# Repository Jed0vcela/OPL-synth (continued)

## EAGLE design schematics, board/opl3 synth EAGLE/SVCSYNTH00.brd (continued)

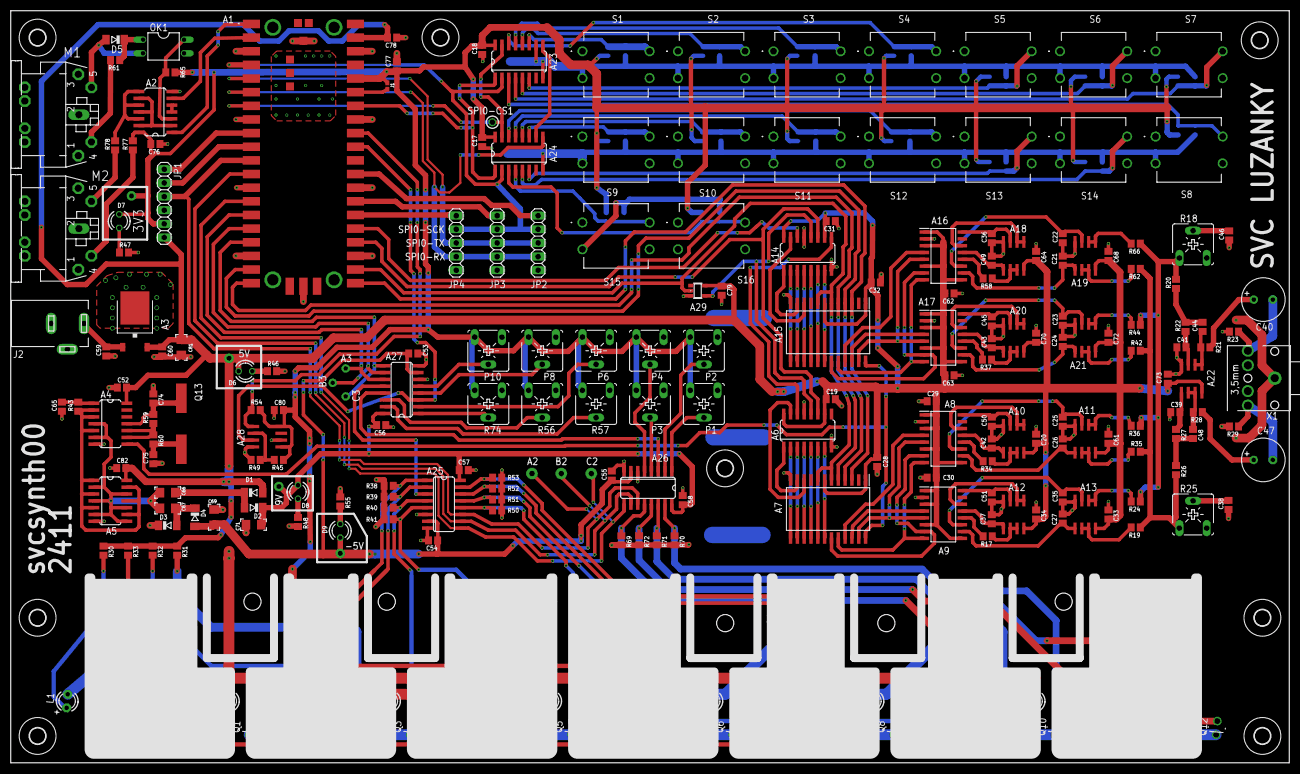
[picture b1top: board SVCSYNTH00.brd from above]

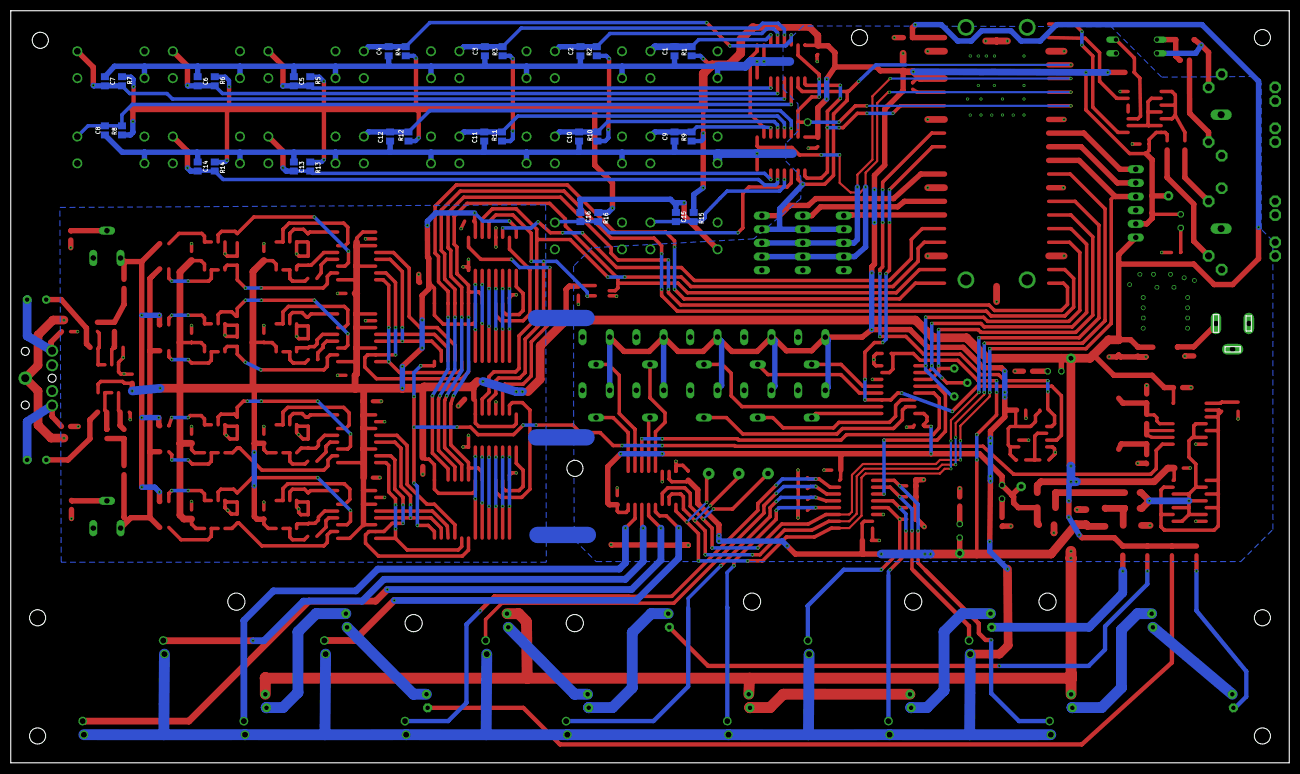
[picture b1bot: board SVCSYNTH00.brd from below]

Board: 2 copper layers, 238.0 x 140.0 mm, 267 parts (32 on the bottom side), 187 nets.

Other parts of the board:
U$8, U$10, U$11, U$13, U$14, U$15, U$17, U$18: 3,0

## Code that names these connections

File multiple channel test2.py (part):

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# Assign chip select (CS) pin and initialize it high
a0 = Pin(14, Pin.OUT)	#OPL3	14
a1 = Pin(15, Pin.OUT)	#OPL3	15
latch = Pin(17, Pin.OUT)#OPL3	17
reset = Pin(16, Pin.OUT)#OPL3 initiel clear
shift_latch = Pin(22, Pin.OUT)#shift register
load = Pin(28, Pin.OUT)	#shift register - buttons
cs1 = Pin(5, Pin.OUT)	#shift register - buttons
adc1 = machine.ADC(26)    #analog multiplexer - potentiometrs and keys
A2 = Pin(8, Pin.OUT)    #analog multiplexer
B2 = Pin(9, Pin.OUT)    #analog multiplexer
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
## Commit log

2025-05-17 upload
2025-06-02 upload
    synthetizer based on OPL3 and RPI pico
